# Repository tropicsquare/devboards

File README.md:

# TROPIC01 devboards
Welcome, PCB designers! 

This repository collects all resources for development boards which we designed with our TROPIC01 secure element. All PCB designs are freely available under **[CERN-OHL-P-2.0](https://ohwr.org/cernohl) Open Hardware license**. We encourage you to re-use designs, modify, or build your own boards!

> [!TIP]
> **Looking for code examples, ready to get started?** Head over to [libtropic](https://github.com/tropicsquare/libtropic) and pick a tutorial that matches your interests. Whether you're new to secure elements or building production systems, you'll find step-by-step guides to get you up and running quickly.

| Product name                      | HW resources                   | Description                           | Image  |
|:---------------------------------:|:------------------------------:|:-------------------------------------:|:------:|
| **TROPIC01 USB Devkit**           | [View](./TROPIC01_USB_Devkit/)          | Suitable for TROPIC01 evaluation over USB. Besides the default functionality of SPI-UART translator which you can plug into PC and evaluate tropic on your laptop by using its serial port, this devkit is also capable of running USB application, because it contain also application MCU. This is ideal starting point for developing own USB application with TROPIC01. |  |
| **TROPIC01 Raspberry Pi Shield**  | [View](./TROPIC01_Raspberry_Pi_Shield/) | Chip is wired to SPI port pins commonly used on Raspberry Pi, ideally use this shield if you want to evaluate on `Raspberry Pi` or some other `Linux SBC` with the `Raspberry Pi` compatible header.  |  |
| **TROPIC01 Mini Board**           | [View](./TROPIC01_Mini_Board/)          | Minimalistic PCB breakout board for TROPIC01, designed to be soldered directly on host PCB, keeping the size small but still handy to hand solder. Suitable for placing on custom made shields or prototyping when PCB space is scarce. |  |
| **TROPIC01 Arduino Shield**       | [View](./TROPIC01_Arduino_Shield/)      | Chip is wired to SPI port pins commonly used on arduino compatible boards. Ideally use this shield if you want to evaluate on prototype which has `Arduino` header. |  |
| **TROPIC01 SECURE TROPIC CLICK**  | [View](./TROPIC01_SECURE_TROPIC_CLICK/) | Tthis is a third party devboard, with the similar functionality as other shields, but with another form factor. Fits into mikroBUS socket, or could be wired over wires as needed.|  |

## Using These Designs

Each particular board folder contains complete design files for all released revisions:
- **Schematics** (`.kicad_sch`) - Showing how components are wired together
- **PCB layouts** (`.kicad_pcb`) - Design of the PCB - how components are physically placed on the PCB
- **BOMs** - Component lists with part numbers
- **Gerbers** - Manufacturing files for PCB fabrication

You're free to use these as reference, modify for your needs, or manufacture your own boards.

> [!IMPORTANT]
> Some devboards include firmware in their folders. Note that firmware or its parts may be under various licensing schemes - see the [licensing section](#license) below for details.

## FAQ

See [FAQ.md](FAQ.md)

## Support & Warranty

These designs and devkits are provided as-is for evaluation and prototyping. No warranties are provided, and no production certifications (e.g., CE/FCC) are implied. Support is best-effort; for code examples and guidance, see [libtropic](https://github.com/tropicsquare/libtropic).

## License

This repository does not contain only PCB resources, but in some cases also HW which comes with devkit. Each part is under different license, more details in following table:

| Component        | License  | Applies To                                                                                          |
|:-----------------|:---------|:----------------------------------------------------------------------------------------------------|
| **PCB Hardware**            | [CERN-OHL-P-2.0](LICENSE.txt) | TROPIC01_Arduino_Shield/, TROPIC01_Raspberry_Pi_Shield/, TROPIC01_Mini_Board/, TROPIC01_USB_Devkit/PCB/ |
| **Firmware**                | [BSD-3-Clause-Clear](LICENSES/FIRMWARE-LICENSE.txt) | TROPIC01_USB_Devkit/firmwares/                         |
| **Third-party USB library** | Specific | TROPIC01_USB_Devkit/firmwares/firmware_B/sdk/ - See [LICENSES/NOTICE.txt](LICENSES/NOTICE.txt)    |

## About TROPIC01

For more information about the TROPIC01 secure element, please see the official documentation:

*   [TROPIC01 Development resources](https://github.com/tropicsquare/tropic01/tree/main/)
*   [TROPIC01 Website](https://www.tropicsquare.com/tropic01)

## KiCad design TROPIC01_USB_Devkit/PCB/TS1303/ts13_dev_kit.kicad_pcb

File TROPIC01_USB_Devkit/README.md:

# TROPIC01 USB Devkit

This repository contains **hardware** design files for the TROPIC01 USB Devkit.

> [!TIP]
> **Looking for code examples, ready to get started?** Head over to [libtropic](https://github.com/tropicsquare/libtropic) and pick a tutorial that matches your interests. Whether you're new to secure elements or building production systems, you'll find step-by-step guides to get you up and running quickly.

## PCB Revisions + BOMs

Following folders contain schematics, layouts, BOMs and gerber files.

- **PCB [TS1301](./PCB/TS1301/)**
- **PCB [TS1302](./PCB/TS1302/)**
- **PCB [TS1303](./PCB/TS1303/)**

## Product Versions

| Product version | PCB Tracking  | PCB Revision  | MCU        | TROPIC01 Part Number | BOM               | Firmware                          | Picture                      | Availability |
|:----:|:------:|:----------:|:---------------:|:-------------:|:-------------------------------:|:---------------------------------:|:-------------------------------------:|:-----:|
| 3.2  | none   | **TS1303** | STM32U5 (512kB) | TR01-C2P-T301 | [BOM](./PCB/TS1303/bom/bom.csv) | [FW B](./firmwares/firmware_B/)   | [Top View](./PCB/TS1303/img/top.png)  | [BUY HERE](https://www.tropicsquare.com/order-devkit)  |
| 3.1  | none   | **TS1303** | STM32U5 (512kB) | TR01-C2P-T103 | [BOM](./PCB/TS1303/bom/bom.csv) | [FW B](./firmwares/firmware_B/)   | [Top View](./PCB/TS1303/img/top.png)  | DEPRECATED  |
| 3.0  | none   | **TS1303** | STM32U5 (512kB) | TR01-C2P-T202 | [BOM](./PCB/TS1303/bom/bom.csv) | [FW B](./firmwares/firmware_B/)   | [Top View](./PCB/TS1303/img/top.png)  | DEPRECATED  |
| 2.0  | none   | **TS1302** | STM32U5 (256kB) | TR01-C2P-T101 | [BOM](./PCB/TS1302/bom/bom.csv) | [FW B](./firmwares/firmware_B/)   | [Top View](./PCB/TS1302/img/top.png)  | DEPRECATED  |
| 1.0  | none   | **TS1301** | STM32F1 (256kB) | TR01-B2S-T005 | [BOM](./PCB/TS1301/bom/bom.csv) | [FW A](./firmwares/firmware_A/)   | [Top View](./PCB/TS1301/img/top.png)  | DEPRECATED  |
## PCB Specifications

Common specifications for all revisions:
- **Layers**: 2-layer
- **Thickness**: 1.0 mm
- **Material**: FR4
- **Solder Mask**: Blue
- **Silkscreen**: Yes (top and bottom)

### Assembly Notes

Standard SMD components (0805 size):
- Resistor tolerance: 5% (unless specified)
- Capacitor tolerance: 20% (unless specified)

## About TROPIC01

For more information about the TROPIC01 secure element, please see the official documentation:

*   [TROPIC01 Development resources](https://github.com/tropicsquare/tropic01/tree/main/)
*   [TROPIC01 Website](https://www.tropicsquare.com/tropic01)

## Support & Warranty

This devkit is provided as-is for evaluation and prototyping. No warranties are provided, and no production certifications (e.g., CE/FCC) are implied. Community-level support only; for examples and tutorials, visit [libtropic](https://github.com/tropicsquare/libtropic).

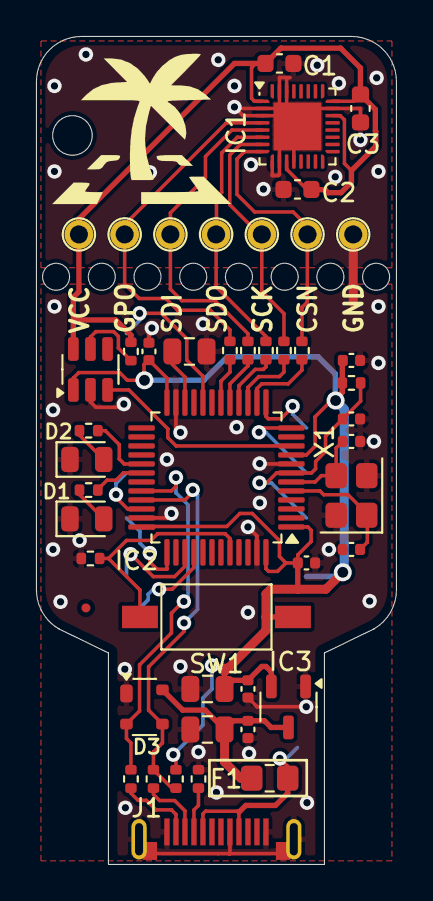
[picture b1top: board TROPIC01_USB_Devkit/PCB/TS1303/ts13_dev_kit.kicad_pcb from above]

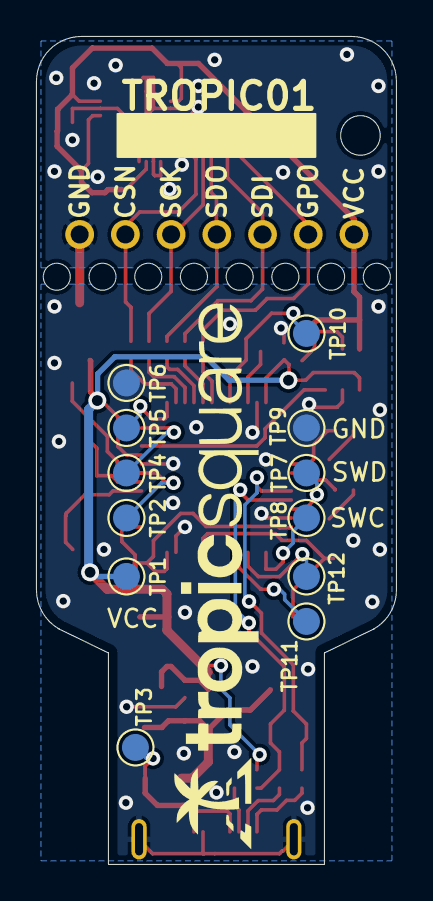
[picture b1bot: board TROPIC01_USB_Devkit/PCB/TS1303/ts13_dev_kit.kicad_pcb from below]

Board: 2 copper layers, 20.0 x 46.0 mm, 70 parts (13 on the bottom side), 38 nets.

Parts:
C1, C2, C3: 100n/603; C_0603_1608Metric
C4, C7, C14: 4u7/16V; C_0805_2012Metric
C5, C6, C9, C13: 100n; C_0402_1005Metric
C8, C10: 10n; C_0402_1005Metric
C11, C12: 10p; C_0402_1005Metric
D1: LED_R; LED_0805_2012Metric
D2: LED_G; LED_0805_2012Metric
D3: PRTR5V0U2X; SOT-143
F1: Fuse 500mA; R_0805_2012Metric_Pad1.20x1.40mm_HandSolder
FID1: Fiducial; Fiducial_0.5mm_Mask1mm
G1: logo; tropicsquare_palm_10
G2: logo; tropicsquare_logo_7
H1, H2, H3, H4, H5, H6, H7, H8: hole; Hole_1.5mm
H9: hole 2.2mm; Hole_2.2mm
IC1: TROPIC01_chip; QFN-32-1EP_4x4mm_P0.4mm_EP2.65x2.65mm
IC2: STM32U535CCTx; LQFP-48_7x7mm_P0.5mm
IC3: TPS7A0533PDBZR; SOT-23-3
IC4: TPS22917DBV; SOT-23-6
J1: USB_C_Plug; USB_C_plug_UP20CFGFL-P12
PAD1, PAD2, PAD3, PAD4, PAD5, PAD6, PAD7: TP; pad_1mm
R1: 33k; R_0402_1005Metric
R2, R3, R4, R5, R6, R7, R13, R14: 1k; R_0402_1005Metric
R8: 5k1; R_0402_1005Metric
R9, R10: 10R; R_0402_1005Metric
R11: 1k5; R_0402_1005Metric
R12: 220R; R_0402_1005Metric
SW1: tact switch; button_PTS636_M25SMTR
TP1, TP2, TP3, TP4, TP5, TP6, TP7, TP8, TP9, TP10, TP11, TP12: TP; TestPoint_1.5mm_noth
X1: 8MHz; Crystal_SMD_3225-4Pin_3.2x2.5mm

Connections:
/BOOT0: IC2.44 (PH3), R6.1, SW1.2
/GPO: IC2.18 (PB0), R2.2
/LED_G: IC2.29 (PA8), R14.2
/LED_R: IC2.30 (PA9), R13.2
/NRST: C10.1, IC2.7 (NRST), R1.2, TP2.1
/SPI_CS: IC2.14 (PA4), R7.2
/SPI_MISO: IC2.16 (PA6), R4.2
/SPI_MOSI: IC2.17 (PA7), R3.2
/SPI_SCK: IC2.15 (PA5), R5.2
/SWCLK: IC2.37 (PA14), TP8.1
/SWDIO: IC2.34 (PA13), TP7.1
/T_PWR_ON: IC2.10 (PA0), IC4.3 (ON)
/U2_RX: IC2.13 (PA3), TP5.1
/U2_TX: IC2.12 (PA2), TP4.1
/USB_N: D3.2 (I/O1), IC2.32 (PA11), R9.2
/USB_P: D3.3 (I/O2), IC2.33 (PA12), R10.2, R11.2
/USB_PWR_5V: C4.1, C5.1, D3.4 (VCC), F1.1, IC3.3 (VI)
GND: C1.1, C2.1, C3.1, C4.2, C5.2, C6.2, C7.2, C8.1, C9.1, C10.2, C11.2, C12.2, C13.1, C14.2, D1.1 (K), D2.1 (K), D3.1 (GND), IC1.2 (GND), IC1.3 (PULLDN), IC1.9 (PULLDN), IC1.10 (PULLDN), IC1.12 (GND), IC1.23 (GND), IC1.30 (PULLDN), IC1.31 (PULLDN), IC1.33 (TP), IC2.8 (VSSA), IC2.23 (VSS), IC2.35 (VSS), IC2.47 (VSS), IC3.1 (GND), IC4.2 (GND), J1.A1 (GND), J1.A12 (GND), J1.B12 (GND), J1.S1 (SHIELD), PAD2.1, R6.2, R8.2, TP6.1, TP9.1, X1.2, X1.4
unnamed: D1.2 (A), R13.1
unnamed: D2.2 (A), R14.1
unnamed: F1.2, J1.A4 (VBUS), J1.B9 (VBUS), TP3.1
unnamed: IC1.8 (CSN), PAD4.1, R7.1
unnamed: IC1.4 (GPO), PAD3.1, R2.1
unnamed: IC1.7 (SCK), PAD5.1, R5.1
unnamed: IC1.5 (SDI), PAD7.1, R3.1
unnamed: IC1.6 (SDO), PAD6.1, R4.1
unnamed: IC2.20 (PB2), TP10.1
unnamed: IC2.39 (PB3), TP12.1
unnamed: IC2.40 (PB4), TP11.1
unnamed: C11.1, IC2.5 (PH0), X1.1
unnamed: C12.1, IC2.6 (PH1), X1.3
unnamed: C14.1, IC2.22 (VCAP)
unnamed: IC4.5 (QOD), R12.1
unnamed: J1.A5 (CC), R8.1
unnamed: J1.A6 (D+), R10.1
unnamed: J1.A7 (D-), R9.1
T_VCC: C1.2, C2.2, C3.2, IC1.1 (VCC), IC1.11 (VCC), IC1.22 (PULLUP), IC1.24 (VCC), IC4.6 (VOUT), PAD1.1, R12.2
VCC: C6.1, C7.1, C8.2, C9.2, C13.2, IC2.1 (VBAT), IC2.9 (VDDA), IC2.24 (VDD), IC2.36 (VDD), IC2.48 (VDD), IC3.2 (VO), IC4.1 (VIN), R1.1, R11.1, SW1.1, TP1.1

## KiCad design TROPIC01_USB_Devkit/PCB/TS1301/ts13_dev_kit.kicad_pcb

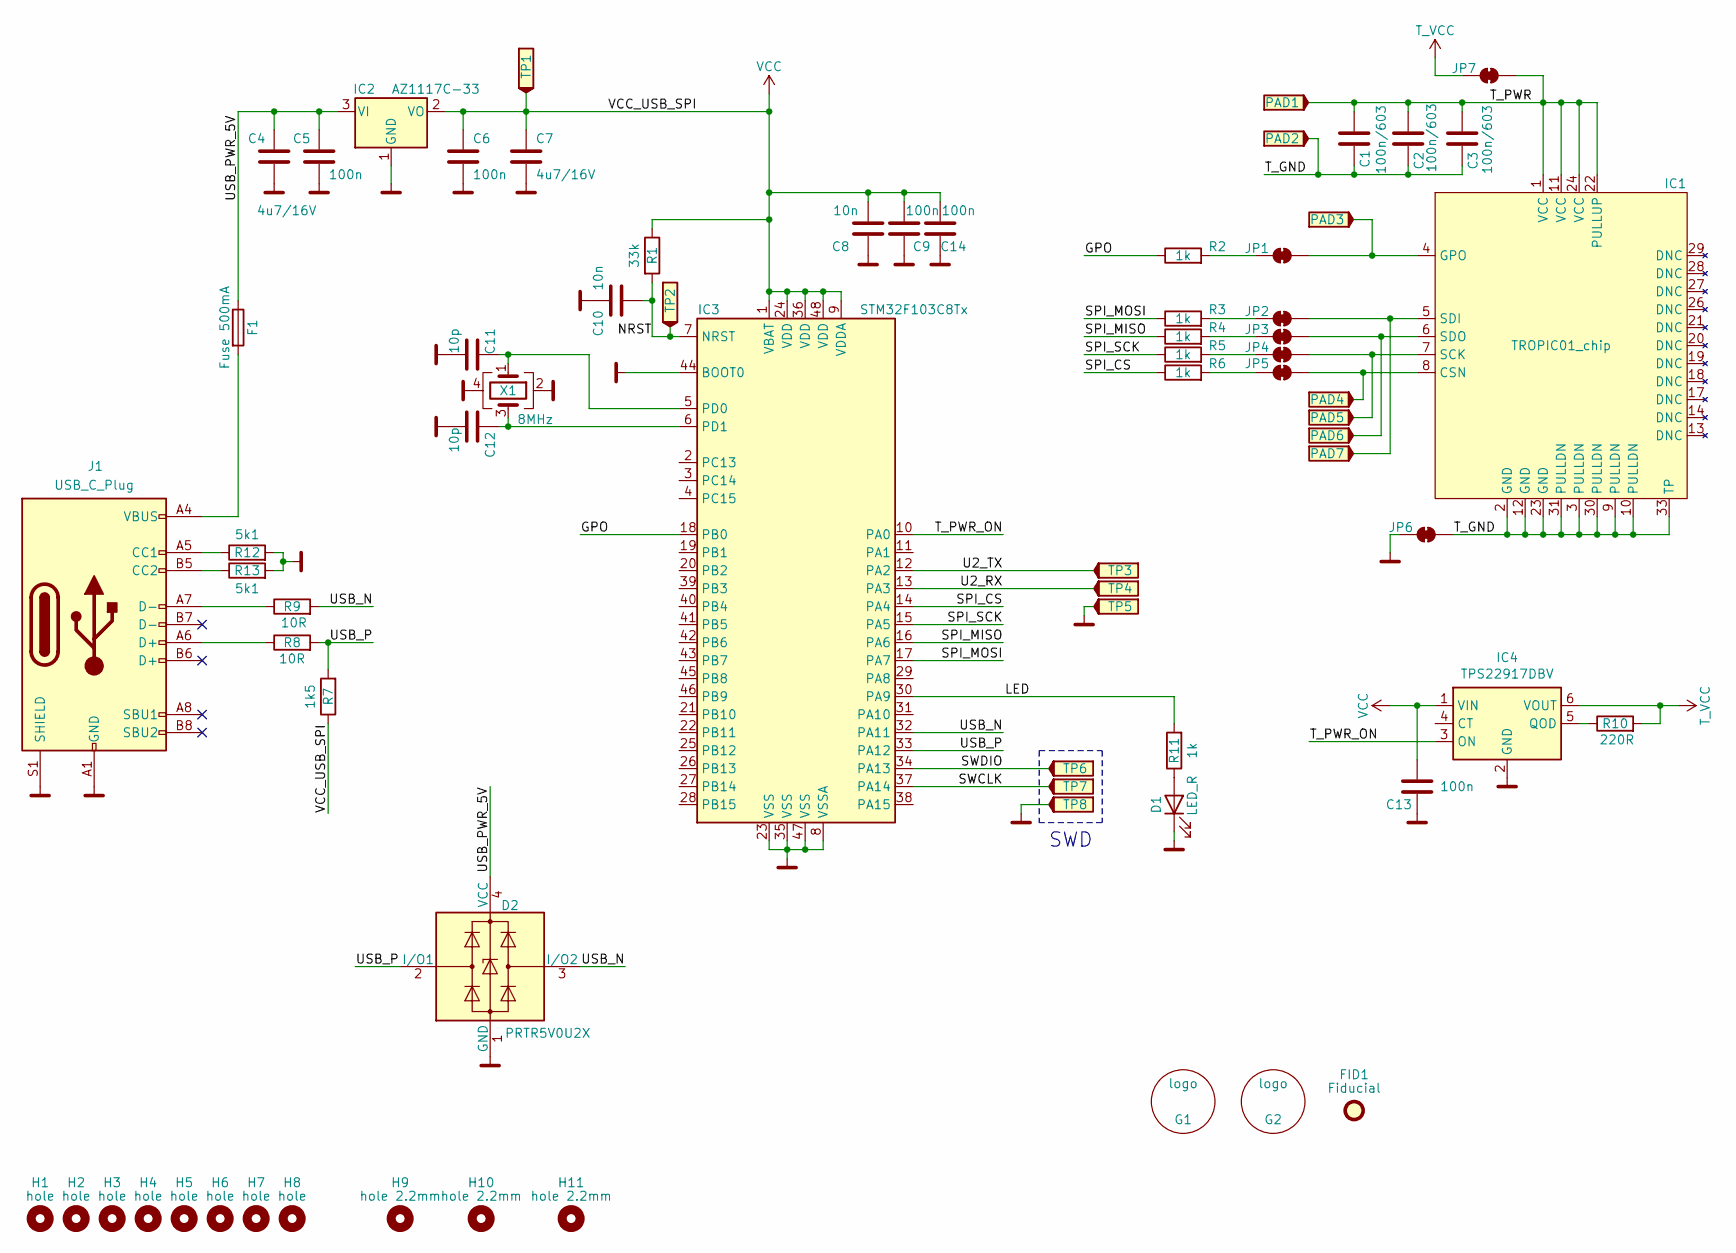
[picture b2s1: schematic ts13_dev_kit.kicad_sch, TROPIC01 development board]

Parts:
C1, C2, C3: 100n/603; C_0603_1608Metric
C4, C7: 4u7/16V; C_0805_2012Metric
C5, C6, C9, C13, C14: 100n; C_0805_2012Metric
C8, C10: 10n; C_0805_2012Metric
C11, C12: 10p; C_0805_2012Metric
D1: LED_R; LED_0805_2012Metric
D2: PRTR5V0U2X; SOT-143
F1: Fuse 500mA; R_0805_2012Metric_Pad1.20x1.40mm_HandSolder
FID1: Fiducial; Fiducial_0.5mm_Mask1mm
G1: logo; tropicsquare_palm_10
G2: logo; tropicsquare_logo_7
H1, H2, H3, H4, H5, H6, H7, H8: hole; Hole_1.45mm
H9, H10, H11: hole 2.2mm; Hole_2.2mm
IC1: TROPIC01_chip; QFN-32-1EP_4x4mm_P0.4mm_EP2.65x2.65mm
IC2: AZ1117C-33; SOT-223
IC3: STM32F103C8Tx; LQFP-48_7x7mm_P0.5mm
IC4: TPS22917DBV; SOT-23-6; LCSC C2681320
J1: USB_C_Plug; USB_C_plug_USB4155_03_C
JP1, JP2, JP3, JP4, JP5, JP6, JP7: SolderJumper_2_Bridged; SolderJumper-2_P1.3mm_Bridged
PAD1, PAD2, PAD3, PAD4, PAD5, PAD6, PAD7: TP; pad_1mm
R1: 33k; R_0805_2012Metric
R2, R3, R4, R5, R6, R11: 1k; R_0805_2012Metric
R7: 1k5; R_0805_2012Metric
R8, R9: 10R; R_0805_2012Metric
R10: 220R; R_0805_2012Metric
R12, R13: 5k1; R_0805_2012Metric
TP1, TP2, TP3, TP4, TP5, TP6, TP7, TP8: TP; TestPoint_1.5mm_noth
X1: 8MHz; Crystal_SMD_0603-4Pin_6.0x3.5mm

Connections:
/GPO: IC3.18 (PB0), R2.1
/LED: IC3.30 (PA9), R11.2
/NRST: C10.1, IC3.7 (NRST), R1.2, TP2.1
/SPI_CS: IC3.14 (PA4), R6.1
/SPI_MISO: IC3.16 (PA6), R4.1
/SPI_MOSI: IC3.17 (PA7), R3.1
/SPI_SCK: IC3.15 (PA5), R5.1
/SWCLK: IC3.37 (PA14), TP7.1
/SWDIO: IC3.34 (PA13), TP6.1
/T_GND: C1.1, C2.1, C3.1, IC1.2 (GND), IC1.3 (PULLDN), IC1.9 (PULLDN), IC1.10 (PULLDN), IC1.12 (GND), IC1.23 (GND), IC1.30 (PULLDN), IC1.31 (PULLDN), IC1.33 (TP), JP6.2 (B), PAD2.1
/T_PWR: C1.2, C2.2, C3.2, IC1.1 (VCC), IC1.11 (VCC), IC1.22 (PULLUP), IC1.24 (VCC), JP7.2 (B), PAD1.1
/T_PWR_ON: IC3.10 (PA0), IC4.3 (ON)
/U2_RX: IC3.13 (PA3), TP4.1
/U2_TX: IC3.12 (PA2), TP3.1
/USB_N: D2.3 (I/O2), IC3.32 (PA11), R9.2
/USB_P: D2.2 (I/O1), IC3.33 (PA12), R7.2, R8.2
/USB_PWR_5V: C4.1, C5.1, D2.4 (VCC), F1.1, IC2.3 (VI)
GND: C4.2, C5.2, C6.2, C7.2, C8.1, C9.1, C10.2, C11.2, C12.2, C13.1, C14.1, D1.1 (K), D2.1 (GND), IC2.1 (GND), IC3.8 (VSSA), IC3.23 (VSS), IC3.35 (VSS), IC3.44 (BOOT0), IC3.47 (VSS), IC4.2 (GND), J1.A1 (GND), J1.A12 (GND), J1.B1 (GND), J1.B12 (GND), J1.S1 (SHIELD), JP6.1 (A), R12.2, R13.2, TP5.1, TP8.1, X1.2, X1.4
unnamed: D1.2 (A), R11.1
unnamed: F1.2, J1.A4 (VBUS), J1.A9 (VBUS), J1.B4 (VBUS), J1.B9 (VBUS)
unnamed: IC1.8 (CSN), JP5.2 (B), PAD4.1
unnamed: IC1.4 (GPO), JP1.2 (B), PAD3.1
unnamed: IC1.7 (SCK), JP4.2 (B), PAD5.1
unnamed: IC1.5 (SDI), JP2.2 (B), PAD7.1
unnamed: IC1.6 (SDO), JP3.2 (B), PAD6.1
unnamed: C11.1, IC3.5 (PD0), X1.1
unnamed: C12.1, IC3.6 (PD1), X1.3
unnamed: IC4.5 (QOD), R10.1
unnamed: J1.A5 (CC1), R12.1
unnamed: J1.B5 (CC2), R13.1
unnamed: J1.A6 (D+), R8.1
unnamed: J1.A7 (D-), R9.1
unnamed: JP1.1 (A), R2.2
unnamed: JP2.1 (A), R3.2
unnamed: JP3.1 (A), R4.2
unnamed: JP4.1 (A), R5.2
unnamed: JP5.1 (A), R6.2
T_VCC: IC4.6 (VOUT), JP7.1 (A), R10.2
VCC: C6.1, C7.1, C8.2, C9.2, C13.2, C14.2, IC2.2 (VO), IC3.1 (VBAT), IC3.9 (VDDA), IC3.24 (VDD), IC3.36 (VDD), IC3.48 (VDD), IC4.1 (VIN), R1.1, R7.1, TP1.1

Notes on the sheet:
SWD

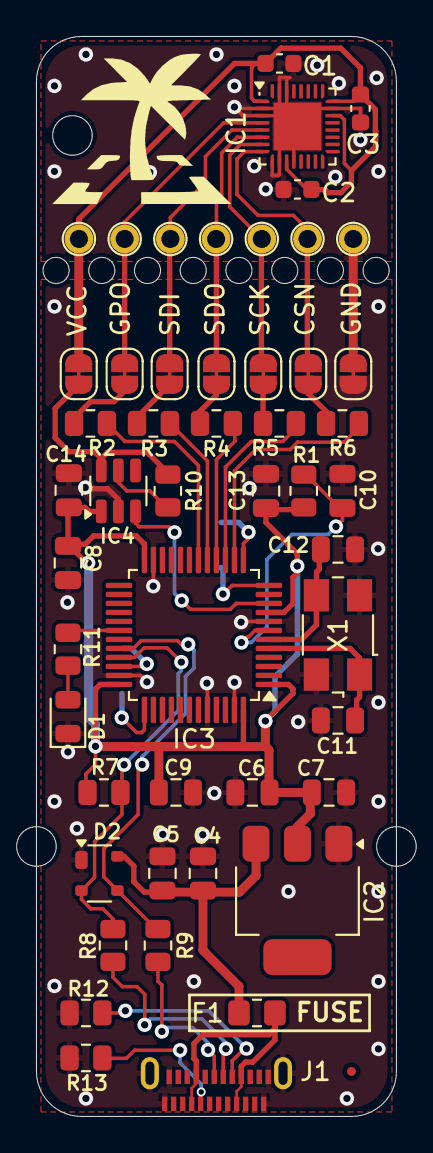
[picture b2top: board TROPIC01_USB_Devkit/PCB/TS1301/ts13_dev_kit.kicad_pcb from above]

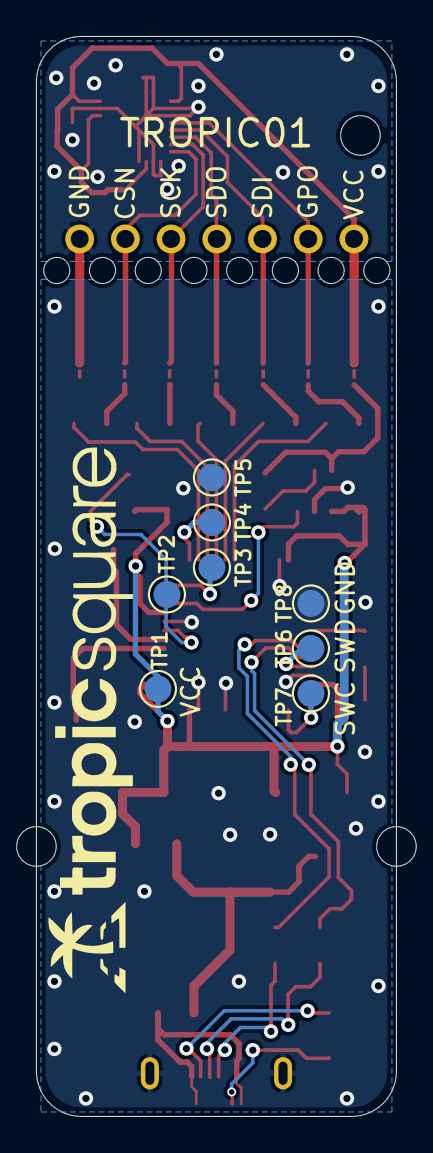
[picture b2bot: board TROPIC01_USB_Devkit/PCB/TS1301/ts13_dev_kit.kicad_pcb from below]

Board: 2 copper layers, 20.0 x 60.0 mm, 72 parts (9 on the bottom side), 39 nets.

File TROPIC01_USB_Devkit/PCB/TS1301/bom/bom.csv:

"Reference","Value","Footprint","Qty","DNP","OC_MOUSER"
"C1,C2,C3","100n/603","Capacitor_SMD:C_0603_1608Metric","3","","80-C0603104K3RAC7411 "
"C4,C7","4u7/16V","Capacitor_SMD:C_0805_2012Metric","2","","187-CL21A475KAQNNNE"
"C5,C6,C9,C13,C14","100n","Capacitor_SMD:C_0805_2012Metric","5","","187-CL21B104KBFNNNE"
"C8,C10","10n","Capacitor_SMD:C_0805_2012Metric","2","","187-CL21B103KCANNNC"
"C11,C12","10p","Capacitor_SMD:C_0805_2012Metric","2","","187-CL21C100CBANNNC"
"D1","LED_R","LED_SMD:LED_0805_2012Metric","1","","710-150080RS75000"
"D2","PRTR5V0U2X","Package_TO_SOT_SMD:SOT-143","1","","771-PRTR5V0U2X-T/R"
"F1","Fuse 500mA","Resistor_SMD:R_0805_2012Metric_Pad1.20x1.40mm_HandSolder","1","","594-MFU0805FF00500P1"
"IC1","TROPIC01_chip","tropic01_chip:QFN-32-1EP_4x4mm_P0.4mm_EP2.65x2.65mm","1","",""
"IC2","AZ1117C-33","Package_TO_SOT_SMD:SOT-223","1","","621-AZ1117CH-3.3TRG1"
"IC3","STM32F103C8Tx","Package_QFP:LQFP-48_7x7mm_P0.5mm","1","","511-STM32F103C8T6"
"IC4","TPS22917DBV","Package_TO_SOT_SMD:SOT-23-6","1","","595-TPS22917DBVR"
"J1","USB_C_Plug","_con_misc:USB_C_plug_USB4155_03_C","1","","640-USB4155-03C "
"R1","33k","Resistor_SMD:R_0805_2012Metric","1","","603-RC0805FR-1333KL"
"R2,R3,R4,R5,R6,R11","1k","Resistor_SMD:R_0805_2012Metric","6","","603-RC0805JR-071KL"
"R7","1k5","Resistor_SMD:R_0805_2012Metric","1","","279-CRGCQ0805F10R"
"R8,R9","10R","Resistor_SMD:R_0805_2012Metric","2","","279-CRGCQ0805F10R"
"R10","220R","Resistor_SMD:R_0805_2012Metric","1","","603-RC0805JR-07220RL"
"R12,R13","5k1","Resistor_SMD:R_0805_2012Metric","2","","652-CR0805FX-5101ELF"
"X1","8MHz","Crystal:Crystal_SMD_0603-4Pin_6.0x3.5mm","1","","774-406C35D08M00000"

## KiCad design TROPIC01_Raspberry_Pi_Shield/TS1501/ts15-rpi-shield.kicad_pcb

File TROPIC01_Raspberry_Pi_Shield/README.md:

# TROPIC01 Raspberry Pi Shield

This repository contains **hardware** design files for the TROPIC01 Raspberry Pi Shield.

> [!TIP]
> **Looking for code examples, ready to get started?** Head over to [libtropic](https://github.com/tropicsquare/libtropic) and pick a tutorial that matches your interests. Whether you're new to secure elements or building production systems, you'll find step-by-step guides to get you up and running quickly.

## PCB Revisions + BOMs

Following folder contains schematics, layouts, BOMs and gerber files.

- **PCB [TS1501](./TS1501/)**

## Product Versions

| Product version | PCB Tracking | PCB Revision | TROPIC01 Part Number | BOM          | Picture            | Availability |
|:-------:|:-----------:|:------------:|:--------------------:|:------------------------------:|:-----------------------:|:-----:|
| 1.3     | none        | **TS1501**   | TR01-C2P-T301  | [BOM](./TS1501/bom/bom_variant_chip_1.3.csv) | [Top View](./TS1501/img/top.png)    | [BUY HERE](https://www.tropicsquare.com/order-devkit)  |
| 1.2     | none        | **TS1501**   | TR01-C2P-T103  | [BOM](./TS1501/bom/bom_variant_chip.csv)     | [Top View](./TS1501/img/top.png)    | DEPRECATED  |
| 1.1     | none        | **TS1501**   | TR01-C2P-T101  | [BOM](./TS1501/bom/bom_variant_chip.csv)     | [Top View](./TS1501/img/top.png)    | DEPRECATED  |
| 1.0     | none        | **TS1501**   | TR01-B2S-T005  | [BOM](./TS1501/bom/bom_variant_chip.csv)     | [Top View](./TS1501/img/top.png)    | DEPRECATED  |

## About TROPIC01

For more information about the TROPIC01 secure element, please see the official documentation:

*   [TROPIC01 Development resources](https://github.com/tropicsquare/tropic01/tree/main/)
*   [TROPIC01 Website](https://www.tropicsquare.com/tropic01)

## Support & Warranty

This shield is provided as-is for evaluation and prototyping. No warranties are provided, and no production certifications (e.g., CE/FCC) are implied. Community-level support only; for examples and tutorials, visit [libtropic](https://github.com/tropicsquare/libtropic).

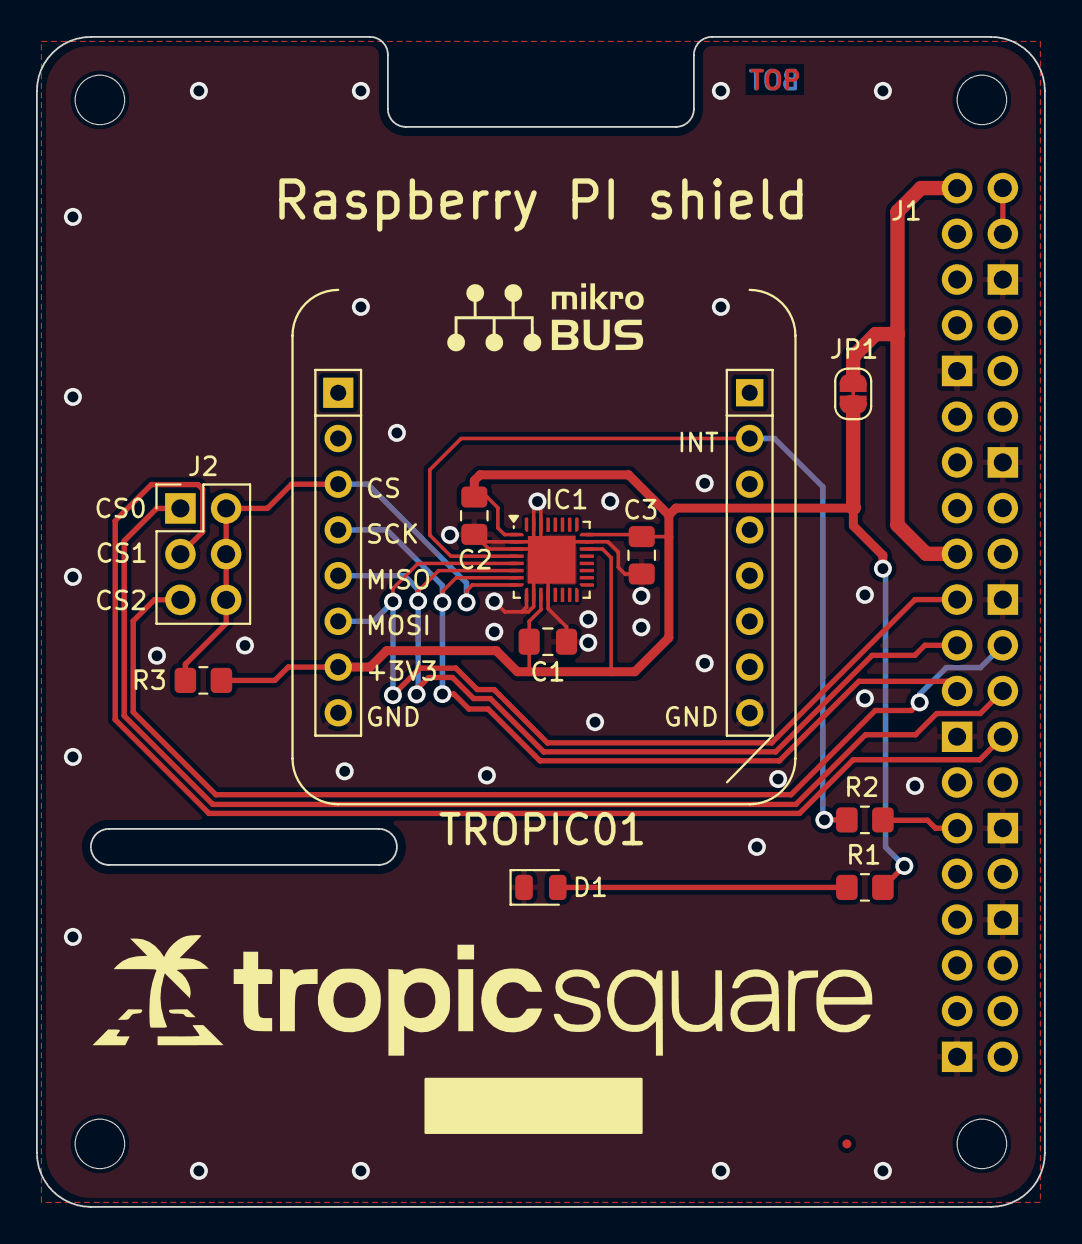
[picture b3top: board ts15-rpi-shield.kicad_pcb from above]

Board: 2 copper layers, 56.0 x 65.0 mm, 14 parts (0 on the bottom side), 14 nets.

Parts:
C1, C2, C3: 100n; C_0805_2012Metric_Pad1.18x1.45mm_HandSolder
CON1: TROPIC01; TROPIC01_mikrobus
D1: LED_G; LED_0805_2012Metric
FID1: Fiducial; Fiducial_0.5mm_Mask1mm
G1: logo; tropicsquare_logo
IC1: TROPIC01_chip; QFN-32-1EP_4x4mm_P0.4mm_EP2.65x2.65mm
J1: RPI socket; RPI_Hat_B+
J2: CS select jumper switch; PinHeader_2x03_P2.54mm_Vertical
JP1: SolderJumper_2_Bridged; SolderJumper-2_P1.3mm_Bridged
R1, R2: 1k; R_0805_2012Metric_Pad1.20x1.40mm_HandSolder
R3: 47k; R_0805_2012Metric_Pad1.20x1.40mm_HandSolder

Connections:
+5V: J1.2, J1.4
/GPIO5: J1.29, R2.2
/GPIO25: J1.22, J2.5
/GPO: CON1.P15 (INT), IC1.4 (GPO), R2.1
/SPI_CE0: J1.24, J2.1
/SPI_CE1: J1.26, J2.3
/SPI_CS: CON1.P3 (CS), IC1.8 (CSN), J2.2, J2.4, J2.6, R3.1
/SPI_MISO: CON1.P5 (MISO), IC1.6 (SDO), J1.21
/SPI_MOSI: CON1.P6 (MOSI), IC1.5 (SDI), J1.19
/SPI_SCK: CON1.P4 (SCK), IC1.7 (SCK), J1.23
GND: C1.1, C2.1, C3.1, CON1.P8 (GND1), CON1.P9 (GND2), D1.1 (K), IC1.2 (GND), IC1.3 (PULLDN), IC1.9 (PULLDN), IC1.10 (PULLDN), IC1.12 (GND), IC1.23 (GND), IC1.30 (PULLDN), IC1.31 (PULLDN), IC1.33 (TP), J1.6, J1.9, J1.14, J1.20, J1.25, J1.30, J1.34, J1.39
unnamed: D1.2 (A), R1.1
unnamed: J1.1, J1.17, JP1.1 (A)
VCC: C1.2, C2.2, C3.2, CON1.P7 (3V3), IC1.1 (VCC), IC1.11 (VCC), IC1.22 (PULLUP), IC1.24 (VCC), JP1.2 (B), R1.2, R3.2

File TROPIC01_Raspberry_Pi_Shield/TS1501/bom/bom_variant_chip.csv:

"Reference","Value","Footprint","Qty","DNP","OC_MOUSER"
"C1,C2,C3","100n","Capacitor_SMD:C_0805_2012Metric_Pad1.18x1.45mm_HandSolder","3","","187-CL21B104KBFNNNE"
"CON1","TROPIC01","ts_mikrobus:TROPIC01_mikrobus","1","DNP","dont assemble"
"D1","LED_G","LED_SMD:LED_0805_2012Metric","1","","710-150080GS75000"
"IC1","TROPIC01_chip","tropic01_chip:QFN-32-1EP_4x4mm_P0.4mm_EP2.65x2.65mm","1","","TR01-C2P-T103"
"J1","RPI socket","shields:RPI_Hat_B+","1","","474-PRT-16764"
"J2","CS select jumper switch","Connector_PinHeader_2.54mm:PinHeader_2x03_P2.54mm_Vertical","1",""," 653-XG8T-0641  + 653-XJ8A-0211"
"R1,R2","1k","Resistor_SMD:R_0805_2012Metric_Pad1.20x1.40mm_HandSolder","2","","603-RC0805JR-071KL"
"R3","47k","Resistor_SMD:R_0805_2012Metric_Pad1.20x1.40mm_HandSolder","1","","603-RC0805JR-0747KL"

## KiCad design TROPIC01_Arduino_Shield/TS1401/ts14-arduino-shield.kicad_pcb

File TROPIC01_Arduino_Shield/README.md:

# TROPIC01 Arduino Shield

This repository contains **hardware** design files for the TROPIC01 Arduino Shield.

> [!TIP]
> **Looking for code examples, ready to get started?** Head over to [libtropic](https://github.com/tropicsquare/libtropic) and pick a tutorial that matches your interests. Whether you're new to secure elements or building production systems, you'll find step-by-step guides to get you up and running quickly.

## PCB Revisions + BOMs

Following folder contains schematics, layouts, BOMs and gerber files.

- **PCB [TS1401](./TS1401/)**

## Product Versions

| Product version   | PCB Tracking    | PCB Revision | Product Variant | TROPIC01 Part Number  | BOM                                     | Picture                             | Availability |
|:-------:|:-------:|:--------------:|:------------------------------:|:----------------:|:--------------------------------------------:|:-----------------------------------:|:-----:|
| 1.2     | none    | **TS1401**     | Assembled with MikroBUS socket | TR01-C2P-T103    | [BOM](./TS1401/bom/bom_variant_microbus.csv) | [Top View](./TS1401/img/top.png)    | [BUY HERE](https://www.tropicsquare.com/order-devkit)       |
| 1.1     | E254630 SL1 |**TS1401**  | Assembled with chip            | TR01-C2P-T101    | [BOM](./TS1401/bom/bom_variant_chip.csv)     | [Top View](./TS1401/img/top.png)    | [BUY HERE](https://www.tropicsquare.com/order-devkit)       |
| 1.0     | E254630 SL1 | **TS1401** | Assembled with chip            | TR01-B2S-T005    | [BOM](./TS1401/bom/bom_variant_chip.csv)     | [Top View](./TS1401/img/top.png)    | DEPRECATED  |

## About TROPIC01

For more information about the TROPIC01 secure element, please see the official documentation:

*   [TROPIC01 Development resources](https://github.com/tropicsquare/tropic01/tree/main/)
*   [TROPIC01 Website](https://www.tropicsquare.com/tropic01)

## Support & Warranty

This shield is provided as-is for evaluation and prototyping. No warranties are provided, and no production certifications (e.g., CE/FCC) are implied. Community-level support only; for examples and tutorials, visit [libtropic](https://github.com/tropicsquare/libtropic).

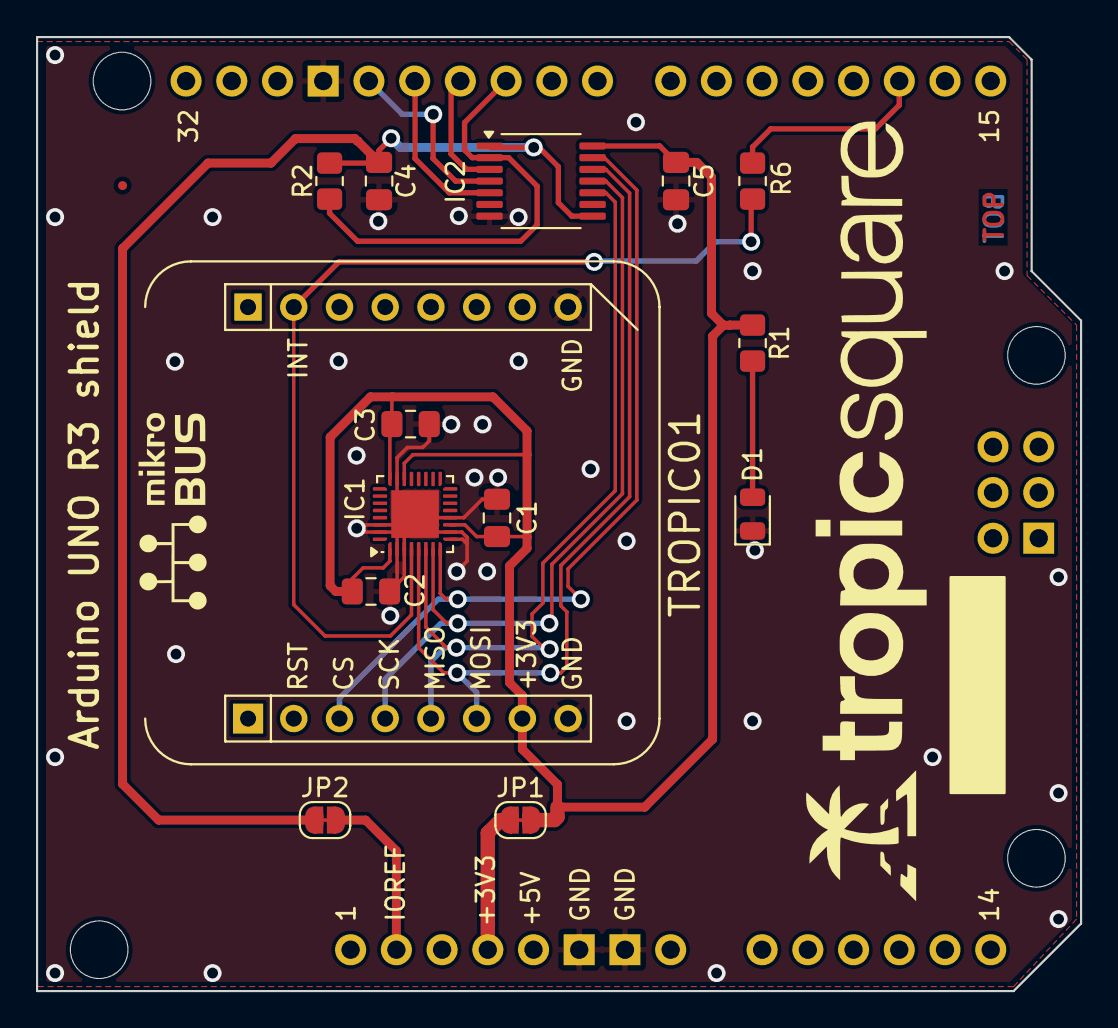
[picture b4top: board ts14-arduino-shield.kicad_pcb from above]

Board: 2 copper layers, 58.0 x 53.0 mm, 17 parts (0 on the bottom side), 16 nets.

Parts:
C1, C2, C3, C4, C5: 100n; C_0805_2012Metric_Pad1.18x1.45mm_HandSolder
CON1: TROPIC01; TROPIC01_mikrobus
D1: LED_G; LED_0805_2012Metric
FID1: Fiducial; Fiducial_0.5mm_Mask1mm
G1: logo; tropicsquare_logo
IC1: TROPIC01_chip; QFN-32-1EP_4x4mm_P0.4mm_EP2.65x2.65mm
IC2: TXU0304PWR; TSSOP-14_4.4x5mm_P0.65mm
JP1, JP2: SolderJumper_2_Bridged; SolderJumper-2_P1.3mm_Bridged
R1, R6: 1k; R_0805_2012Metric_Pad1.20x1.40mm_HandSolder
R2: 47k; R_0805_2012Metric_Pad1.20x1.40mm_HandSolder
Shield1: Arduino_Uno_R3_Shield

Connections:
/5V_INT: R6.2, Shield1.D2 (D2_INT0)
/5V_SPI_CS: IC2.2 (A1_IN), R2.1, Shield1.D10 (D10_CS)
/5V_SPI_MISO: IC2.5 (A4_OUT), Shield1.D12
/5V_SPI_MOSI: IC2.3 (A2_IN), Shield1.D11
/5V_SPI_SCK: IC2.4 (A3_IN), Shield1.D13
/GPO: CON1.P15 (INT), IC1.4 (GPO), R6.1
/SPI_CS: CON1.P3 (CS), IC1.8 (CSN), IC2.13 (B1_OUT)
/SPI_MISO: CON1.P5 (MISO), IC1.6 (SDO), IC2.10 (B4_IN)
/SPI_MOSI: CON1.P6 (MOSI), IC1.5 (SDI), IC2.12 (B2_OUT)
/SPI_SCK: CON1.P4 (SCK), IC1.7 (SCK), IC2.11 (B3_OUT)
/VCC_SPI_IO: C4.1, IC2.1 (VCCA), IC2.8 (OE), JP2.1 (A), R2.2
GND: C1.1, C2.1, C3.1, C4.2, C5.1, CON1.P8 (GND1), CON1.P9 (GND2), D1.1 (K), IC1.2 (GND), IC1.3 (PULLDN), IC1.9 (PULLDN), IC1.10 (PULLDN), IC1.12 (GND), IC1.23 (GND), IC1.30 (PULLDN), IC1.31 (PULLDN), IC1.33 (TP), IC2.7 (GND), Shield1.GND1 (GND), Shield1.GND2 (GND), Shield1.GND3 (GND)
unnamed: D1.2 (A), R1.1
unnamed: JP1.1 (A), Shield1.3V3 (3.3V)
unnamed: JP2.2 (B), Shield1.IORF (IOREF)
VCC: C1.2, C2.2, C3.2, C5.2, CON1.P7 (3V3), IC1.1 (VCC), IC1.11 (VCC), IC1.22 (PULLUP), IC1.24 (VCC), IC2.14 (VCCB), JP1.2 (B), R1.2

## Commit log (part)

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2026-01-15 Initial commit collecting all pcb resources for TROPIC01 devboards to create single repository
2026-01-15 doc: Update readme to contain draft of new version system
2026-01-15 ref: Clean fw files
2026-01-16 ref: Clean up legaci firmware B, commit used files instead of submodule
2026-01-16 feat: Update licensing
2026-01-16 ref: Refactor readme
2026-01-16 feat: Add legacy firmware A files
2026-01-16 feat: Update legacy firmware A files
2026-01-16 feat: Update firmware A legacy files
2026-01-16 feat: Cleanup legacy firmwares
2026-01-16 feat: Cleanup firmware A files, add deleted Legacy headers
2026-01-20 doc: Update README.md
2026-01-20 feat: Add KiCAD library files
2026-01-21 feat: Update KiCAD library, update readme
2026-01-21 feat: Add pictures to main readme
2026-01-21 feat: Update size of images
2026-01-21 ref: Rename KiCAD to KiCad
2026-01-21 feat: Add TS1303 design files
2026-01-21 ref: Rename pcb to PCB, update readmes
2026-01-21 doc: Fix table and typo
2026-01-21 doc: Fix typo
2026-01-21 doc: Refactor readmes
2026-01-22 doc: Update folder names
2026-01-22 doc: Unify readmes for TS1301-2-3
2026-01-22 fix: remove redundant line
2026-01-22 docs: Add folder description for USB Devkit main readme
2026-01-22 doc: Update USB Devkit readme
2026-01-22 doc: Unify devboard readmes and folder names for all devboards
2026-01-22 fix: Update broken links
2026-01-22 doc: Add info about firmware licensing
2026-01-22 fix: Update readme
2026-01-22 doc: Update readmes to be more welcoming
2026-01-22 doc: merge USB devkit readmes int one
2026-01-22 doc: consolidated some readmes
2026-01-22 ref: rename folder
2026-01-22 docs: Update readmes
2026-01-22 fix: Update name for kicad banner
2026-01-22 doc: Update KiCad readme
2026-01-22 doc: Add production photos for all devboards
2026-01-23 ref: Add TROPIC01 to all devboards' names
2026-01-27 fix: Update links after folder renaming
2026-01-27 feat; Add warranty notice
2026-01-29 feat: update PCB marking and TR01 PN allocation to each devkit
2026-02-03 feat: add the missing USB devkit with T202
2026-02-05 ref : swap 2nd and 4th column in table
2026-02-05 feat: Add SECURE TROPIC CLICK devboard
2026-02-05 feat: add MIKRO-E click board variants
2026-02-06 feat: Add SECURE TROPIC CLICK to main readme, update licensing
2026-02-25 feat: Add github action for packaging files, add PR template
2026-02-25 fix: Change branch names to names actually used
2026-02-25 Doc: Change release texts and namings
2026-02-25 doc: Add description to each devboard in a table
2026-02-25 feat: Add Silkscreen rectangle to TS1501
2026-02-25 feat: Add silkscreen rectangle to TS1303
2026-02-25 feat: Add silkscreen rectangle to TS1401
2026-02-25 feat: Add TS1702 files
2026-02-25 feat: Update CI - compressed files now contain license
2026-02-26 doc: Update changelog
